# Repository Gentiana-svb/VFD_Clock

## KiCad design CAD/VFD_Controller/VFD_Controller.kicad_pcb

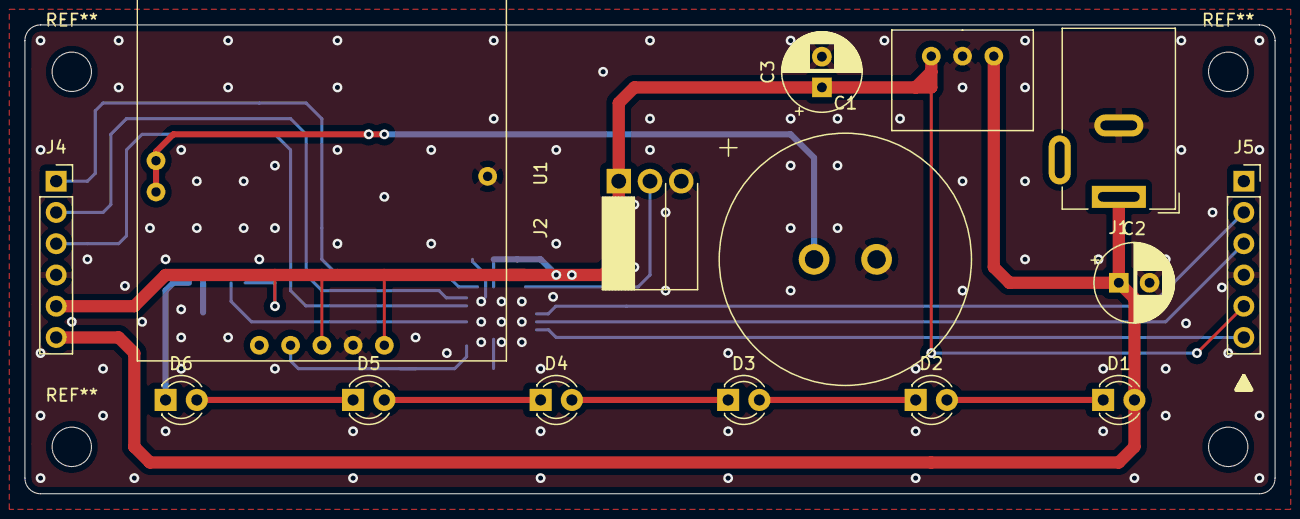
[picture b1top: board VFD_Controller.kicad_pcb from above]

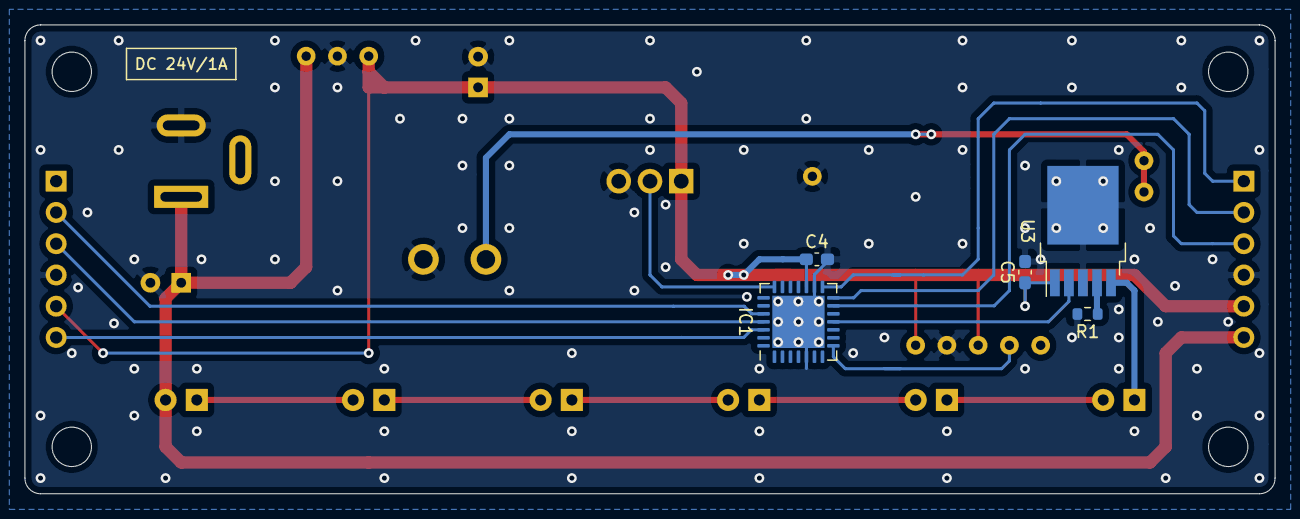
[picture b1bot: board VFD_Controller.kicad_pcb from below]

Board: 2 copper layers, 101.6 x 38.1 mm, 20 parts (5 on the bottom side), 20 nets.

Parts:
C1: 1.5F; EDLC
C2: 22u; CP_Radial_D6.3mm_P2.50mm
C3: 100u; CP_Radial_D6.3mm_P2.50mm
C4, C5: 0.1u; C_0603_1608Metric_Pad1.08x0.95mm_HandSolder
D1, D2, D3, D4, D5, D6: LED; LED_D3.0mm
IC1: PIC18F27Q10; QFN-28-1EP_6x6mm_P0.65mm_EP4.25x4.25mm
J1: Barrel_Jack_Switch; BarrelJack_Wuerth_6941xx301002
J2: SB412A
J4: Conn_01x06; PinSocket_1x06_P2.54mm_Vertical
J5: ICSP; PinSocket_1x06_P2.54mm_Vertical
R1: 20; R_0603_1608Metric
U1: AE-GPS
U2: M78AR033-1; M78AR-1
U3: NJW4617; TO-252-5_TabPin3

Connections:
+3V3: C3.1, C4.1, C5.1, IC1.17, J2.1, J4.5, J5.5, U1.1, U1.3, U2.3, U3.1
+24V: C2.1, D1.2, J1.1, J4.6, U2.1
/LED: IC1.11, U3.2
/MCLR: IC1.26, J5.6
/PGC: IC1.24, J5.2
/PGD: IC1.25, J5.3
/PYRO: IC1.21, J2.2
/RCK: IC1.14, J4.2
/RX: IC1.8, U1.4
/SCK: IC1.15, J4.1
/SI: IC1.13, J4.3
GND: C1.2, C2.2, C3.2, C4.2, C5.2, IC1.5, IC1.16, IC1.29, J1.2, J2.3, J4.4, J5.4, R1.2, U1.2, U1.8, U2.2, U3.3
unnamed: C1.1, U1.6, U1.7
unnamed: D1.1, D2.2
unnamed: D2.1, D3.2
unnamed: D3.1, D4.2
unnamed: D4.1, D5.2
unnamed: D5.1, D6.2
unnamed: D6.1, U3.5
unnamed: R1.1, U3.4

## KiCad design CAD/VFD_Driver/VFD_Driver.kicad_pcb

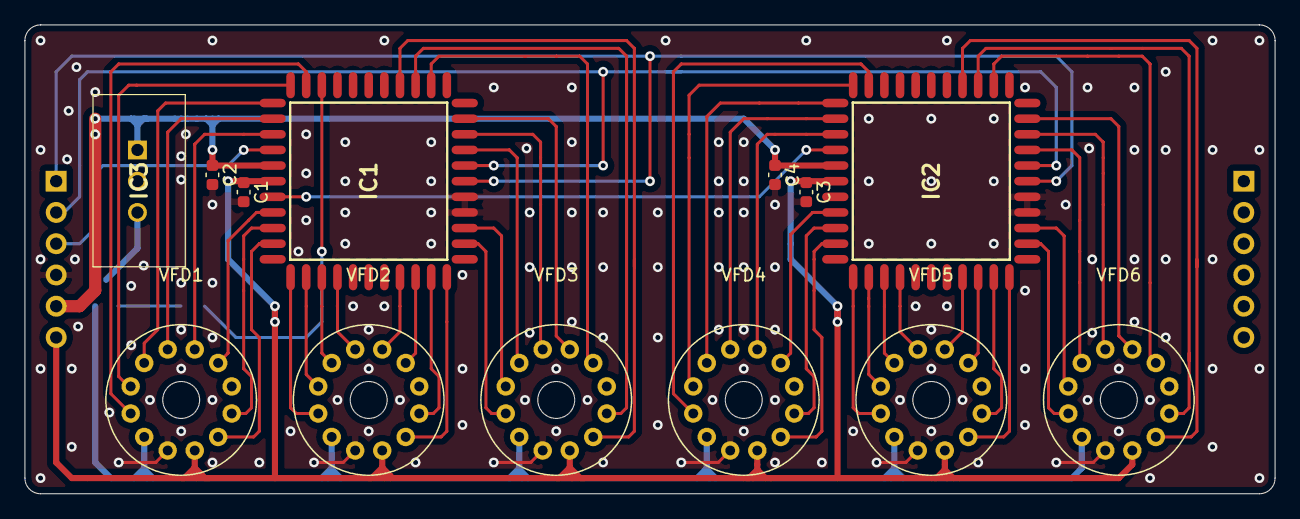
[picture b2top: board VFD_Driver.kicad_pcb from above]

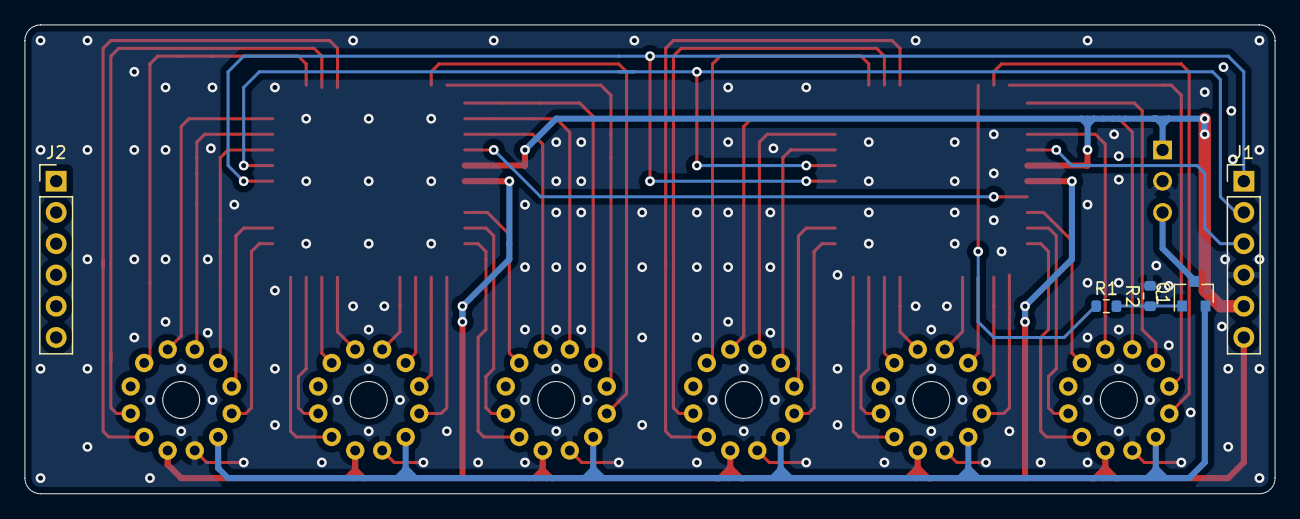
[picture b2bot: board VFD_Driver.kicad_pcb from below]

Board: 2 copper layers, 101.6 x 38.1 mm, 18 parts (5 on the bottom side), 59 nets.

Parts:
C1, C2, C3, C4: 0.1u; C_0603_1608Metric
IC1, IC2: MAX6922; PLCC127P1752X1752X457-44N
IC3: TSR_2-0512; TSR22412
J1, J2: Conn_01x06; PinHeader_1x06_P2.54mm_Vertical
Q1: IRLML6344; SOT-23
R1: 30k; R_0603_1608Metric
R2: 10k; R_0603_1608Metric
VFD1, VFD2, VFD3, VFD4, VFD5, VFD6: IV-6

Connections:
+3V3: C2.1, C4.1, IC1.44, IC2.44, IC3.1, J1.5
+24V: C1.1, C3.1, IC1.1, IC2.1, J1.6, VFD1.9, VFD2.9, VFD3.9, VFD4.9, VFD5.9, VFD6.9
/0_A: IC2.27, VFD6.2
/0_B: IC2.30, VFD6.1
/0_C: IC2.32, VFD6.10
/0_D: IC2.19, VFD6.6
/0_DP: IC2.31, VFD6.11
/0_E: IC2.20, VFD6.5
/0_F: IC2.25, VFD6.4
/0_G: IC2.26, VFD6.3
/1_A: IC2.14, VFD5.2
/1_B: IC2.15, VFD5.1
/1_C: IC2.17, VFD5.10
/1_D: IC2.7, VFD5.6
/1_DP: IC2.16, VFD5.11
/1_E: IC2.8, VFD5.5
/1_F: IC2.9, VFD5.4
/1_G: IC2.10, VFD5.3
/2_A: IC2.42, VFD4.2
/2_B: IC2.3, VFD4.1
/2_C: IC2.5, VFD4.10
/2_D: IC2.38, VFD4.6
/2_DP: IC2.4, VFD4.11
/2_E: IC2.39, VFD4.5
/2_F: IC2.40, VFD4.4
/2_G: IC2.41, VFD4.3
/3_A: IC1.27, VFD3.2
/3_B: IC1.30, VFD3.1
/3_C: IC1.32, VFD3.10
/3_D: IC1.19, VFD3.6
/3_DP: IC1.31, VFD3.11
/3_E: IC1.20, VFD3.5
/3_F: IC1.25, VFD3.4
/3_G: IC1.26, VFD3.3
/4_A: IC1.14, VFD2.2
/4_B: IC1.15, VFD2.1
/4_C: IC1.17, VFD2.10
/4_D: IC1.7, VFD2.6
/4_DP: IC1.16, VFD2.11
/4_E: IC1.8, VFD2.5
/4_F: IC1.9, VFD2.4
/4_G: IC1.10, VFD2.3
/5_A: IC1.42, VFD1.2
/5_B: IC1.3, VFD1.1
/5_C: IC1.5, VFD1.10
/5_D: IC1.38, VFD1.6
/5_DP: IC1.4, VFD1.11
/5_E: IC1.39, VFD1.5
/5_F: IC1.40, VFD1.4
/5_G: IC1.41, VFD1.3
/CASCADE: IC1.2, IC2.43
/H_Control: IC1.37, R1.1
/H_Power: Q1.2, VFD1.7, VFD2.7, VFD3.7, VFD4.7, VFD5.7, VFD6.7
/RCK: IC1.24, IC2.24, J1.2
/SCK: IC1.23, IC2.23, J1.1
/SI: IC1.43, J1.3
GND: C1.2, C2.2, C3.2, C4.2, IC1.21, IC1.22, IC2.21, IC2.22, IC3.2, J1.4, R2.2, VFD1.8, VFD2.8, VFD3.8, VFD4.8, VFD5.8, VFD6.8
unnamed: IC3.3, Q1.3
unnamed: Q1.1, R1.2, R2.1

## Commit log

2021-04-23 Separate PGM
2021-04-23 v2 (working
2021-10-29 add library
